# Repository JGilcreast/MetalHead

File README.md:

An opensource firmware and software drop-in replacement for the 85V Automatic Stirrup Bender by CRS Specialties Inc.
...short story behind the name...

# System Block Diagram

---

# Firmware
### HMI - Zephyr RTOS
* It's preferred to use CLion, 
* [Download](https://apps.microsoft.com/search?query=python&hl=en-US&gl=US) and install the latest version of python
* Install wget and 7Zip so that they're accessible via cmd:
  * `choco install wget 7zip`
* Verify python is accessible via cmd:
  * `python -V`
* Create python virtual environment
  * `cd MetalHead\firmware\interface-board-zephyr`
  * `python -m venv .\.venv`
* Enter python virtual environment
  * `.\.venv\Scripts\activate.bat`
* Update pip (optional)
  * `python.exe -m pip install --upgrade pip`
* Install west
  * `pip install west`
* Initiate the Zephyr-RTOS project
  * `west init`
* Set BOARD to rpi-pico
  * `west config zephyr.board rpi_pico`
* Pull the latest commits from Zephyr's github
  * `west update`
* Export a Zephyr CMake package. This allows CMake to automatically load boilerplate code required for building Zephyr applications.
  * `west zephyr-export`
  * > See: Computer\HKEY_CURRENT_USER\Software\Kitware\CMake\Packages
* Install additional packages need by west
  * `west packages pip --install`
* Install the Zephyr SDK
  * `west sdk install`
* Create a folder for bossac: C:\Program Files (x86)\BOSSA
* Copy bossac.exe to C:\Program Files (x86)\BOSSA
* Add C:\Program Files (x86)\BOSSA to PATH environment (use `sysdm.cpl`)
  * Make sure you can access bossac.exe. Open a new terminal and run: `bossac --help`
* Copy bossac.py from `MetalHead\firmware\interface-board-zephyr` to `MetalHead\firmware\interface-board-zephyr\zephyr\scripts\west_commands\runners`
* Start CLion
* Open our project: MetalHead\firmware\interface-board-zephyr\application
* Configure python interpreter for west
  * Go to File -> Settings -> Languages & Frameworks -> Python
  * Select the python interpreter from the list

To build a pristine copy of the firmware binary:[.gitignore](.gitignore)

  * `cd MetalHead\firmware\interface-board-zephyr`
  * `rmdir /q /s application\build`
  * Go back to CLion and reload West
  * Build, flash, etc

---

# Software
### HMI - Crude Edition

This is a simple unpolished version of the HMI app that will eventually run on the orange pi.
This version is mostly for implementation and testing purposes.
### HMI
The polished version of the HMI app. This app version be able to accomplish the following:
* Must be able to communicate with the interface board bi-directionally
* Display all relevant information in realtime.
* Recognize user input from the custom keypad
* Offer simple 'wizards' that visually guide operators to make common shapes

Nice to have features:
* Auto-update HMI software by communicating to a remote server
* Auto-update interface firmware by communicating to a remote server
* Include a section for custom stirrup calculators/guides
* Include instructional videos on using the machinery

---

# Hardware
### Interface Board

### Keypad

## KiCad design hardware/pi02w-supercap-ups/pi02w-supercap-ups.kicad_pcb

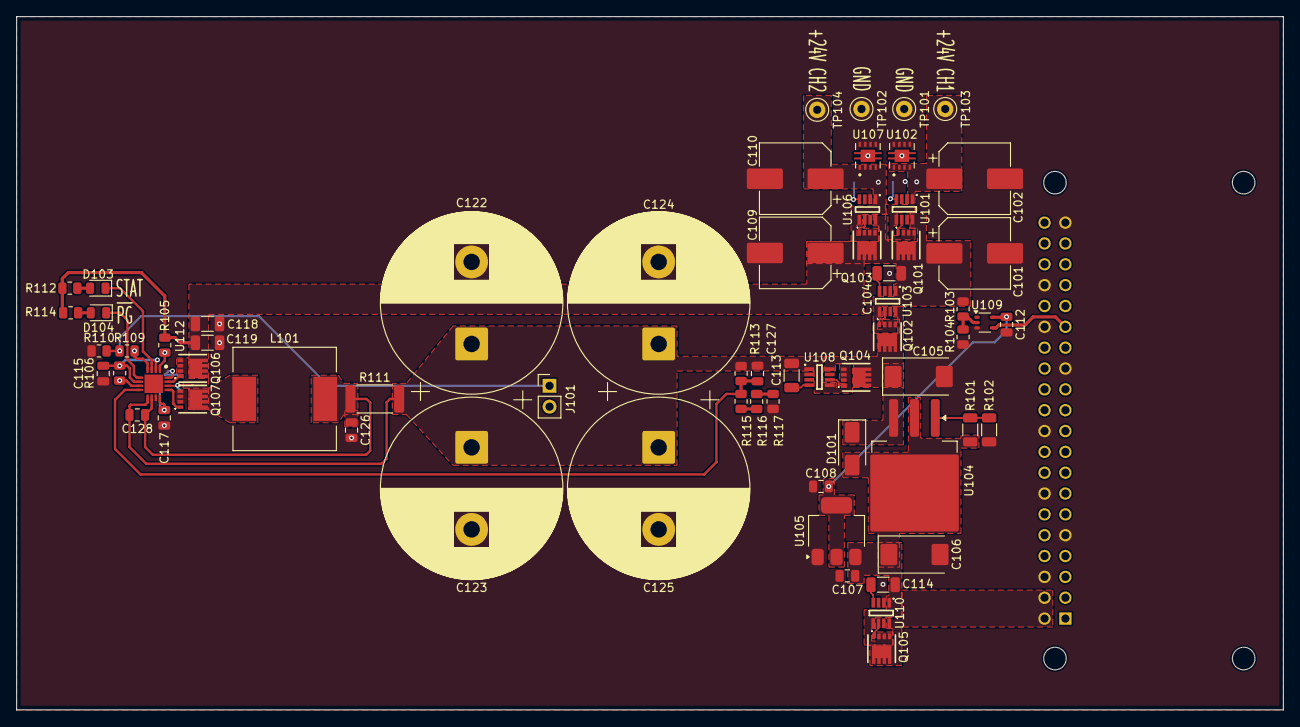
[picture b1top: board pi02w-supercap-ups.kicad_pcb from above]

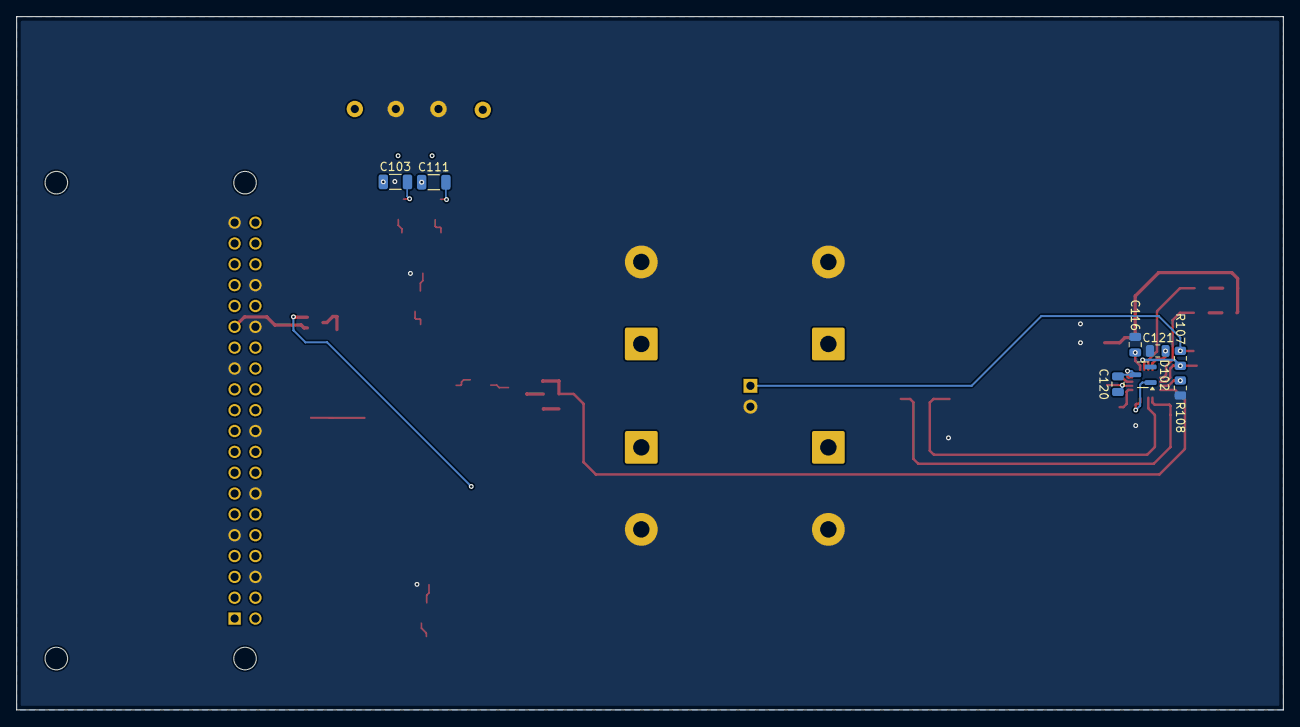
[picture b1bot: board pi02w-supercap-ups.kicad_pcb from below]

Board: 2 copper layers, 154.4 x 84.5 mm, 74 parts (8 on the bottom side), 40 nets.

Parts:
C101, C102, C109, C110: 330uF 25V; CP_Elec_8x10.5
C103, C104, C111, C113, C114: 100nF; C_1206_3216Metric
C105, C106: 10uF 50V; CP_EIA-7343-31_Kemet-D
C107, C108: 100nF; C_0805_2012Metric
C112, C115, C116, C117: 1uF; C_0805_2012Metric
C118, C119: 10uF; C_1206_3216Metric
C120, C121, C126, C128: 0.1uF; C_0805_2012Metric
C122, C123, C124, C125: 22000uF/25V; CP_Radial_D22.0mm_P10.00mm_SnapIn
C127: 22pF; C_0805_2012Metric
D101: 1N4002 M2; D_SMA
D102: BAT54C; SOT-23
D103: RED; LED_0805_2012Metric
D104: GREEN; LED_0805_2012Metric
J101: SEMITEC 103AT-2; PinHeader_1x02_P2.54mm_Vertical
L101: 10uH; L_12x12mm_H8mm
Q101, Q102, Q103, Q104, Q105, Q106, Q107: DMT6007LFG; DMP4013LFG7
R101: 300R; R_1206_3216Metric
R102: 900R; R_1206_3216Metric
R103: 62K; R_0805_2012Metric
R104: 10K; R_0805_2012Metric
R105: 10R; R_0805_2012Metric
R106: 100K; R_0805_2012Metric
R107: 9.31K; R_0805_2012Metric
R108: 22.1K; R_0805_2012Metric
R109: 100R; R_0805_2012Metric
R110: 430K; R_0805_2012Metric
R111: 10mR; R_2512_6332Metric
R112, R114: 2K2; R_0805_2012Metric
R113: 5K1; R_0805_2012Metric
R115: 430R; R_0805_2012Metric
R116: 56R; R_0805_2012Metric
R117: 3R; R_0805_2012Metric
TP101, TP102: 125-00869; TestPoint_Keystone_5000-5004_Miniature
TP103, TP104: 125-00868; TestPoint_Keystone_5000-5004_Miniature
U101, U103, U106, U108, U110: LM74700QDDFRQ1; SOT65P280X110-8N
U102, U107: TVS2701DRBR; IC_TVS2701DRBR
U104: LM1084-ADJ; TO-263-3_TabPin2
U105: AMS1117-3.3; SOT-223-3_TabPin2
U109: 74LVC1G14GW-Q100,1; SOT-353_SC-70-5
U111: RASPBERRY_PI_ZERO_2_W; MODULE_RASPBERRY_PI_ZERO_2_W
U112: BQ24640RVAR; QFN50P350X350X100-17N-D

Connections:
24VCC: C105.1, D101.1 (K), Q102.2 (D), Q104.2 (D), U103.8 (CATHODE), U104.3 (VI), U108.8 (CATHODE)
+3V3: C108.1, C112.1, U105.2 (VO), U109.5 (VCC)
+5V: C106.1, C107.1, C114.1, D101.2 (A), Q105.3 (S), R101.1, U104.2 (VO), U105.3 (VI), U110.1 (EN), U110.5 (ANODE)
+24V: C101.1, C104.1, C109.1, C118.1, C119.1, Q101.2 (D), Q102.3 (S), Q103.2 (D), Q106.2 (D), R103.1, R105.1, R112.1, R114.1, U101.8 (CATHODE), U103.1 (EN), U103.5 (ANODE), U106.8 (CATHODE)
/24VGATE: R103.2, R104.1, U109.2
/BTST: C120.1, D102.3 (K), U112.16 (BTST)
/HIDRV: Q106.1 (G), U112.15 (HIDRV)
/ISET: R106.2, R108.1, U112.7 (ISET)
/LODRV: Q107.1 (G), U112.13 (LODRV)
/PH: C120.2, L101.1, Q106.3 (S), Q107.2 (D), U112.14 (PH)
/PI02W5VCC: Q105.2 (D), U110.8 (CATHODE), U111.2 (5V_2), U111.4 (5V_4)
/PWRSNS: U109.4, U111.29 (GPIO5)
/REGN: C117.1, D102.1 (A), U112.12 (REGN)
/SRP: C126.2, C128.1, L101.2, R111.1, U112.10 (SRP)
/STAT: D103.1 (K), U112.3 (STAT)
/THERM: J101.1, R107.2, R109.1, R110.1
/TS: C121.1, R109.2, U112.4 (TS)
/VCC: C116.1, R105.2, U112.1 (VCC)
/VFB: C127.2, R113.2, R115.1, U112.8 (VFB)
/VREF: C115.1, R106.1, R107.1, U112.2 (CE), U112.6 (VREF)
/~PG: D104.1 (K), U112.5 (~PG)
GND: C101.2, C102.2, C105.2, C106.2, C107.2, C108.2, C109.2, C110.2, C112.2, C115.2, C116.2, C117.2, C118.2, C119.2, C121.2, C122.2, C123.2, C124.2, C125.2, C126.1, J101.2, Q107.3 (S), R102.2, R104.2, R108.2, R110.2, R117.2, TP101.1, TP102.1, U101.2 (GND), U102.5 (GND), U102.6 (GND), U102.7 (GND), U102.8 (GND), U103.2 (GND), U105.1 (GND), U106.2 (GND), U107.5 (GND), U107.6 (GND), U107.7 (GND), U107.8 (GND), U108.2 (GND), U109.3 (GND), U110.2 (GND), U111.6 (GND_6), U111.9 (GND_9), U111.14 (GND_14), U111.20 (GND_20), U111.25 (GND_25), U111.30 (GND_30), U111.34 (GND_34), U111.39 (GND_39), U112.11 (GND), U112.17 (EP)
unnamed: D103.2 (A), R112.2
unnamed: D104.2 (A), R114.2
unnamed: Q101.1 (G), U101.6 (GATE)
unnamed: Q102.1 (G), U103.6 (GATE)
unnamed: Q103.1 (G), U106.6 (GATE)
unnamed: Q104.1 (G), U108.6 (GATE)
unnamed: Q105.1 (G), U110.6 (GATE)
unnamed: R115.2, R116.1
unnamed: R116.2, R117.1
unnamed: C103.2, U101.4 (VCAP)
unnamed: C104.2, U103.4 (VCAP)
unnamed: R101.2, R102.1, U104.1 (ADJ)
unnamed: C111.2, U106.4 (VCAP)
unnamed: C113.2, U108.4 (VCAP)
unnamed: C114.2, U110.4 (VCAP)
RAW24V1: C102.1, C103.1, Q101.3 (S), TP103.1, U101.1 (EN), U101.5 (ANODE), U102.1 (IN), U102.2 (IN), U102.3 (IN), U102.4 (IN)
RAW24V2: C110.1, C111.1, Q103.3 (S), TP104.1, U106.1 (EN), U106.5 (ANODE), U107.1 (IN), U107.2 (IN), U107.3 (IN), U107.4 (IN)
UPS24V: C113.1, C122.1, C123.1, C124.1, C125.1, C127.1, C128.2, Q104.3 (S), R111.2, R113.1, U108.1 (EN), U108.5 (ANODE), U112.9 (SRN)

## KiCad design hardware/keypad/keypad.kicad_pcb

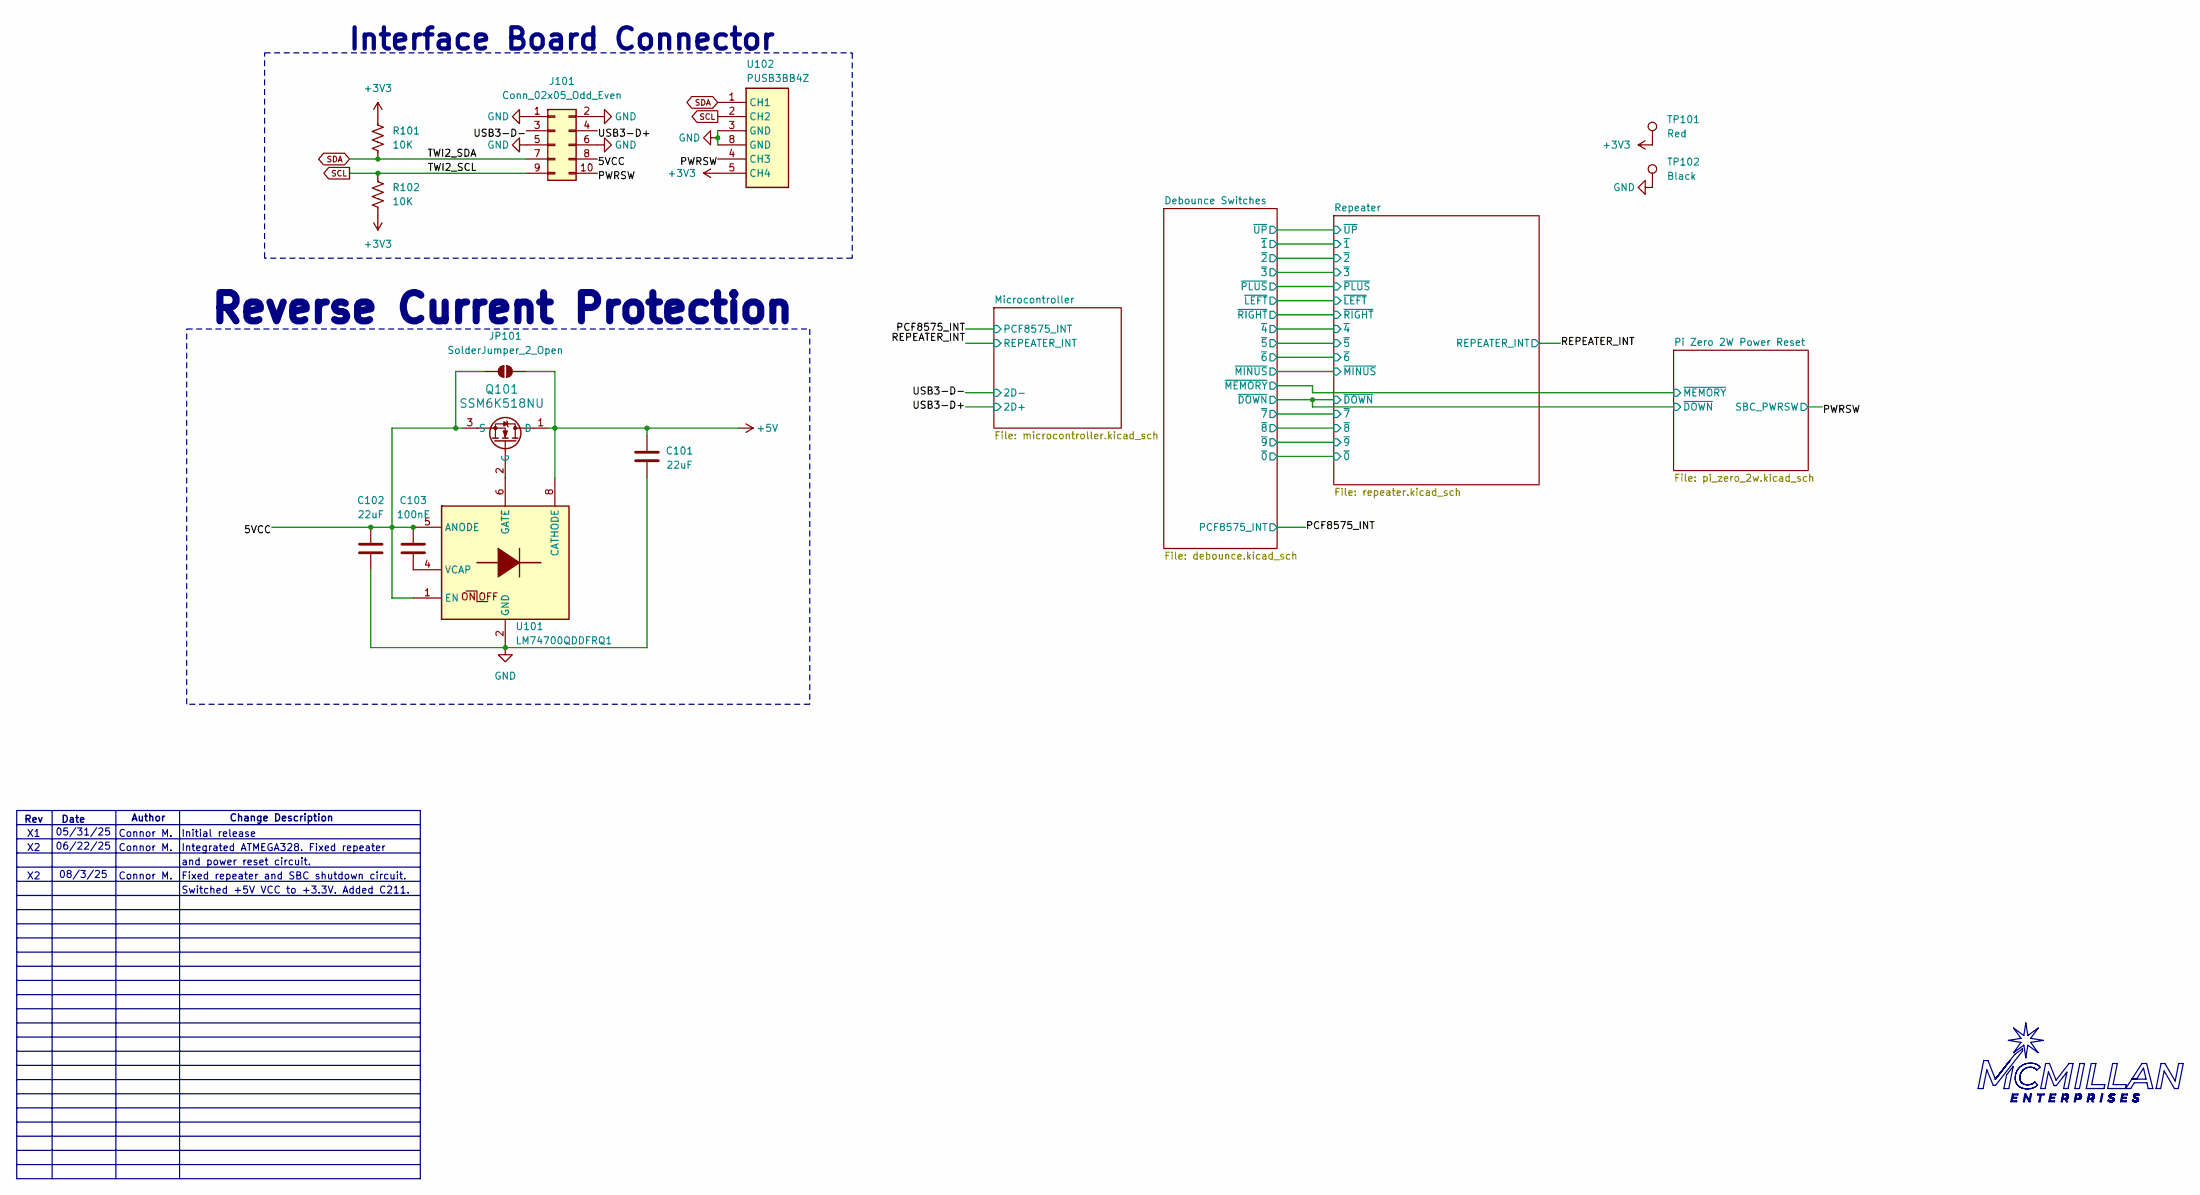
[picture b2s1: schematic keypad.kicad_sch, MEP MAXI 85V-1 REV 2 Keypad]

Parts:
C101, C102: 22uF; C_1206_3216Metric
C103: 100nF; C_1206_3216Metric
J101: Conn_02x05_Odd_Even; IDC-Header_2x05_P2.54mm_Vertical
JP101: SolderJumper_2_Open; SolderJumper-2_P1.3mm_Open_TrianglePad1.0x1.5mm
Q101: SSM6K518NU; SOT-1220UDFN6B_TOS
R101, R102: 10K; R_0805_2012Metric
TP101: Red; TestPoint_Keystone_5000-5004_Miniature
TP102: Black; TestPoint_Keystone_5000-5004_Miniature
U101: LM74700QDDFRQ1; SOT65P280X110-8N; Mouser Part Number 595-LM74700QDDFRQ1
U102: PUSB3BB4Z; SON50P100X250X50-10N; Mouser Part Number 771-PUSB3BB4Z

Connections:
+3V3: R101.1, R102.2, TP101.1, U102.5 (CH4); also elsewhere on the board
/5VCC: C102.1, C103.1, J101.8, JP101.1 (A), Q101.3 (S), U101.1 (EN), U101.5 (ANODE)
/PWRSW: J101.10, U102.4 (CH3); also elsewhere on the board
/USB3-D+: J101.4; also elsewhere on the board
/USB3-D-: J101.3; also elsewhere on the board
GND: C101.2, C102.2, J101.1, J101.2, J101.5, J101.6, TP102.1, U101.2 (GND), U102.3 (GND), U102.8 (GND); also elsewhere on the board
unnamed: C103.2, U101.4 (VCAP)
SCL: J101.9, R102.1, U102.2 (CH2); also elsewhere on the board
SDA: J101.7, R101.2, U102.1 (CH1); also elsewhere on the board

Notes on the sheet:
Change Description
Interface Board Connector
Integrated ATMEGA328. Fixed repeater
Date
Connor M.
and power reset circuit.
Initial release
Switched +5V VCC to +3.3V. Added C211.
08/3/25
Author
06/22/25
Reverse Current Protection
Fixed repeater and SBC shutdown circuit.
Rev
05/31/25

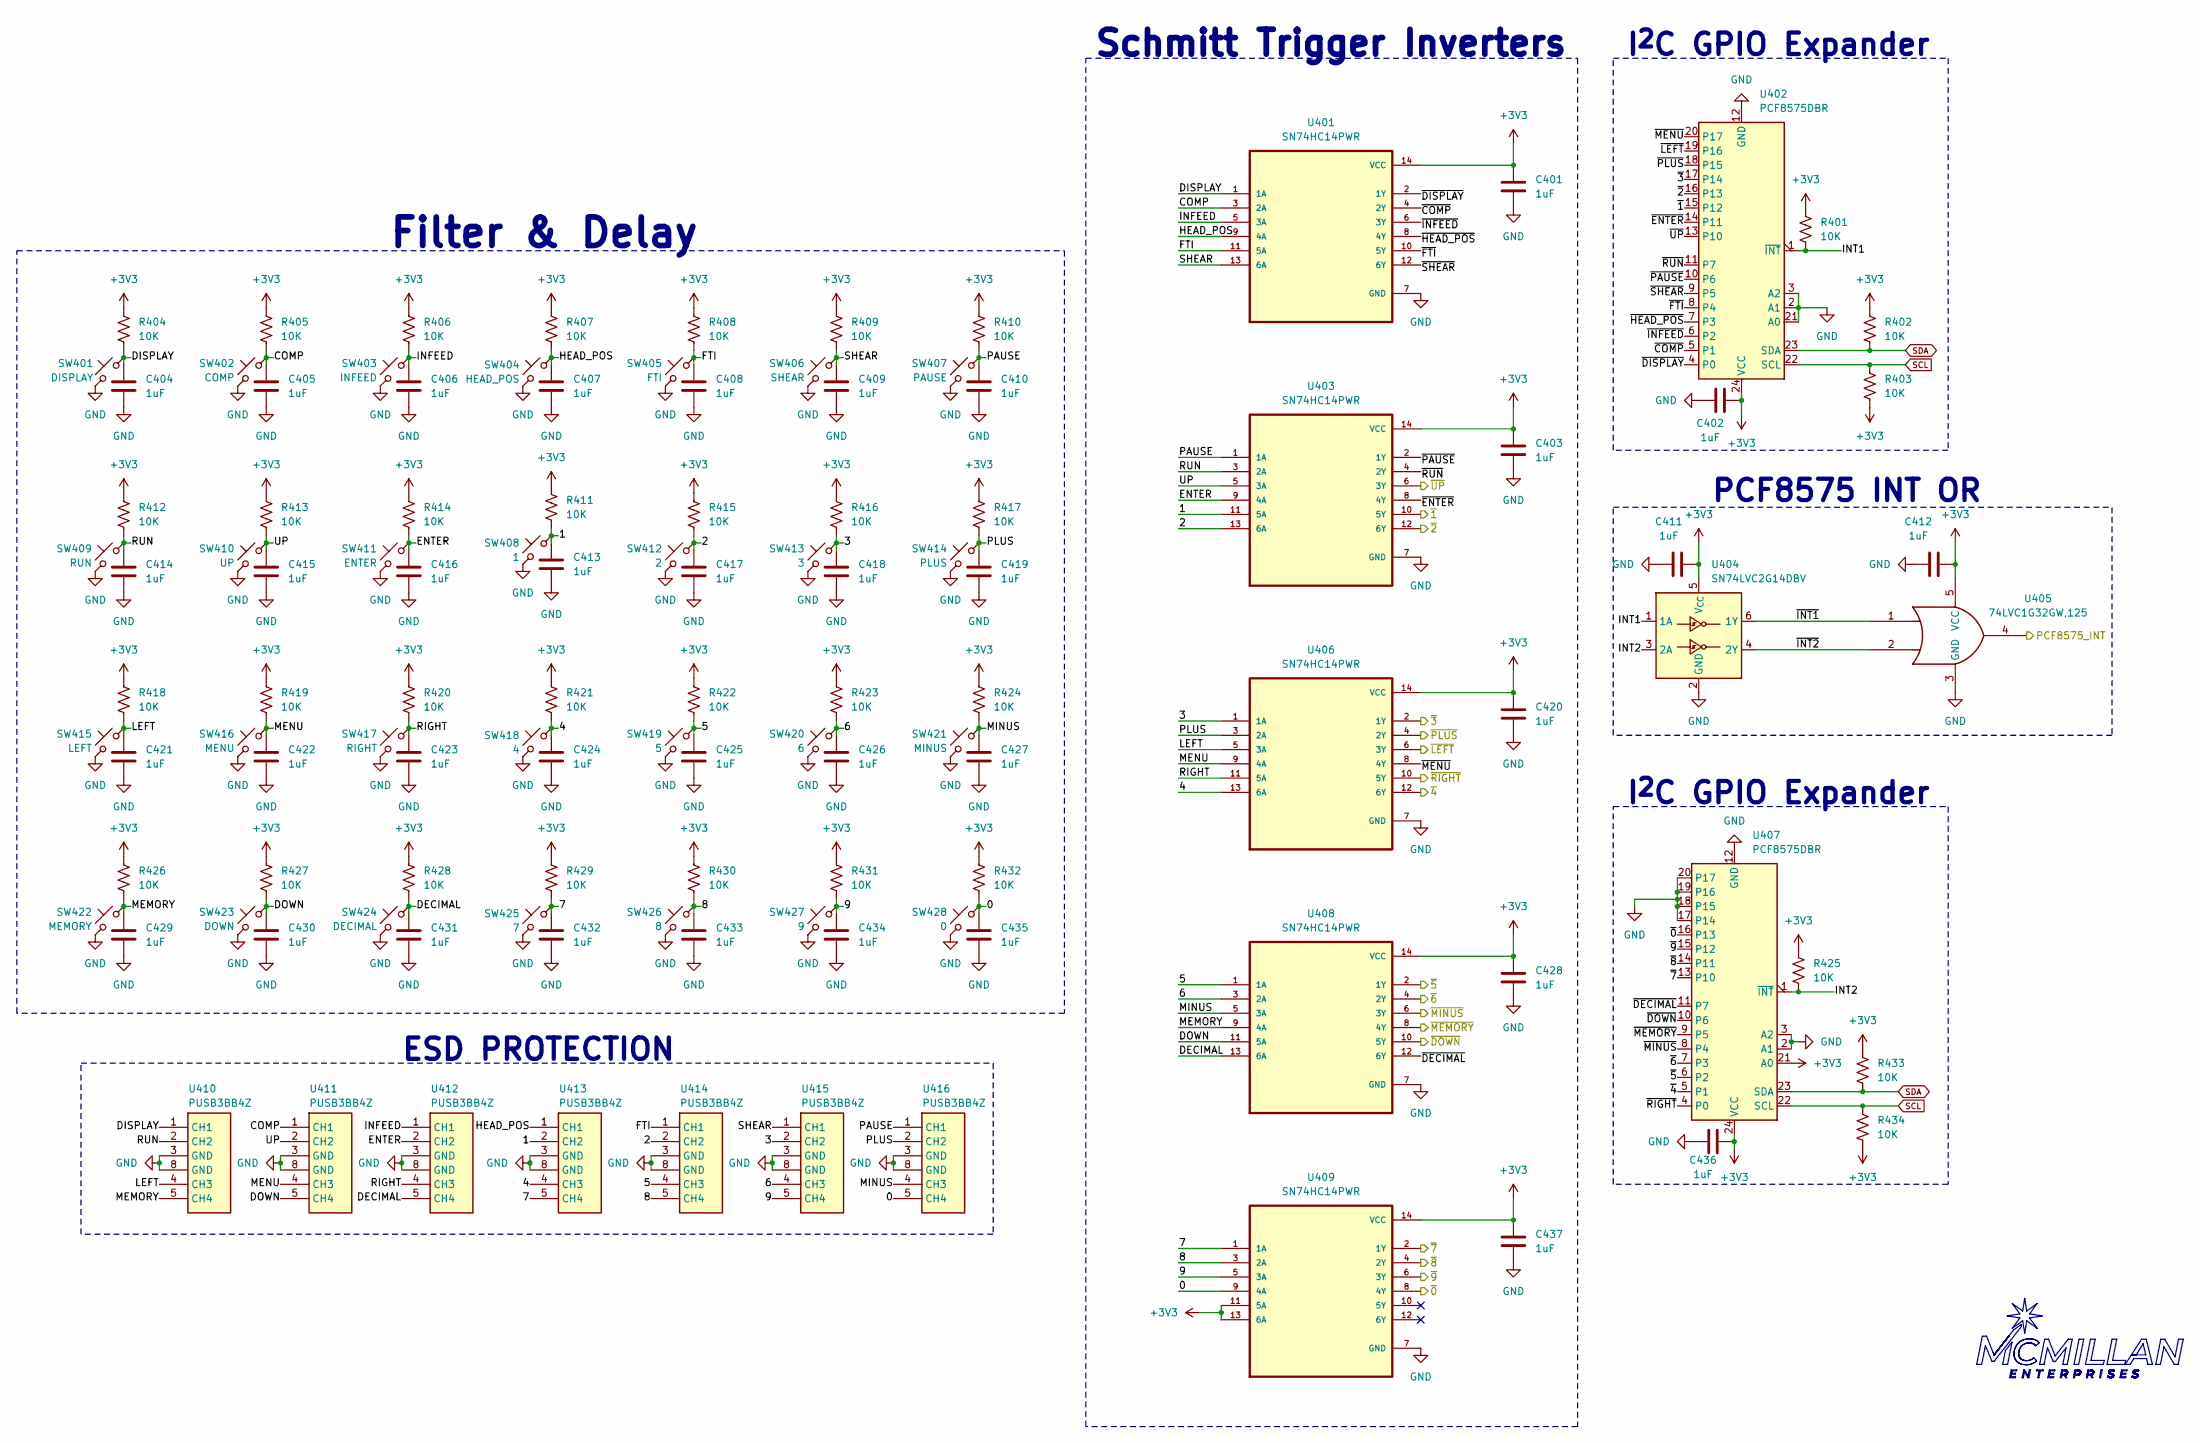
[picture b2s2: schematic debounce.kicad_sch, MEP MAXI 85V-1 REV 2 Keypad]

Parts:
C401, C402, C403, C404, C405, C406, C407, C408, C409, C410, C411, C412, C413, C414, C415, C416, C417, C418, C419, C420, C421, C422, C423, C424, C425, C426, C427, C428, C429, C430, C431, C432, C433, C434, C435, C436, C437: 1uF; C_0805_2012Metric
R401, R402, R403, R404, R405, R406, R407, R408, R409, R410, R411, R412, R413, R414, R415, R416, R417, R418, R419, R420, R421, R422, R423, R424, R425, R426, R427, R428, R429, R430, R431, R432, R433, R434: 10K; R_0805_2012Metric
SW401: DISPLAY; SW_SPST_Omron_B3F-40xx
SW402: COMP; SW_SPST_Omron_B3F-40xx
SW403: INFEED; SW_SPST_Omron_B3F-40xx
SW404: HEAD_POS; SW_SPST_Omron_B3F-40xx
SW405: FTI; SW_SPST_Omron_B3F-40xx
SW406: SHEAR; SW_SPST_Omron_B3F-40xx
SW407: PAUSE; SW_SPST_Omron_B3F-40xx
SW408: 1; SW_SPST_Omron_B3F-40xx
SW409: RUN; SW_SPST_Omron_B3F-40xx
SW410: UP; SW_SPST_Omron_B3F-40xx
SW411: ENTER; SW_SPST_Omron_B3F-40xx
SW412: 2; SW_SPST_Omron_B3F-40xx
SW413: 3; SW_SPST_Omron_B3F-40xx
SW414: PLUS; SW_SPST_Omron_B3F-40xx
SW415: LEFT; SW_SPST_Omron_B3F-40xx
SW416: MENU; SW_SPST_Omron_B3F-40xx
SW417: RIGHT; SW_SPST_Omron_B3F-40xx
SW418: 4; SW_SPST_Omron_B3F-40xx
SW419: 5; SW_SPST_Omron_B3F-40xx
SW420: 6; SW_SPST_Omron_B3F-40xx
SW421: MINUS; SW_SPST_Omron_B3F-40xx
SW422: MEMORY; SW_SPST_Omron_B3F-40xx
SW423: DOWN; SW_SPST_Omron_B3F-40xx
SW424: DECIMAL; SW_SPST_Omron_B3F-40xx
SW425: 7; SW_SPST_Omron_B3F-40xx
SW426: 8; SW_SPST_Omron_B3F-40xx
SW427: 9; SW_SPST_Omron_B3F-40xx
SW428: 0; SW_SPST_Omron_B3F-40xx
U401, U403, U406, U408, U409: SN74HC14PWR; SOP65P640X120-14N
U402, U407: PCF8575DBR; SSOP-24_5.3x8.2mm_P0.65mm
U404: SN74LVC2G14DBV; SOT95P280X145-6N
U405: 74LVC1G32GW,125; SOT-353_SC-70-5
U410, U411, U412, U413, U414, U415, U416: PUSB3BB4Z; SON50P100X250X50-10N; Mouser Part Number 771-PUSB3BB4Z

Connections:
+3V3: C401.1, C402.2, C403.1, C411.2, C412.2, C420.1, C428.1, C436.2, C437.1, R401.1, R402.1, R403.2, R404.1, R405.1, R406.1, R407.1, R408.1, R409.1, R410.1, R411.1, R412.1, R413.1, R414.1, R415.1, R416.1, R417.1, R418.1, R419.1, R420.1, R421.1, R422.1, R423.1, R424.1, R425.1, R426.1, R427.1, R428.1, R429.1, R430.1, R431.1, R432.1, R433.1, R434.2, U401.14 (VCC), U402.24 (VCC), U403.14 (VCC), U404.5 (V_{CC}), U405.5 (VCC), U406.14 (VCC), U407.21 (A0), U407.24 (VCC), U408.14 (VCC), U409.11 (5A), U409.13 (6A), U409.14 (VCC); also elsewhere on the board
/Debounce Switches/0: C435.1, R432.2, SW428.2, U409.9 (4A), U416.5 (CH4)
/Debounce Switches/1: C413.1, R411.2, SW408.2, U403.11 (5A), U413.2 (CH2)
/Debounce Switches/2: C417.1, R415.2, SW412.2, U403.13 (6A), U414.2 (CH2)
/Debounce Switches/3: C418.1, R416.2, SW413.2, U406.1 (1A), U415.2 (CH2)
/Debounce Switches/4: C424.1, R421.2, SW418.2, U406.13 (6A), U413.4 (CH3)
/Debounce Switches/5: C425.1, R422.2, SW419.2, U408.1 (1A), U414.4 (CH3)
/Debounce Switches/6: C426.1, R423.2, SW420.2, U408.3 (2A), U415.4 (CH3)
/Debounce Switches/7: C432.1, R429.2, SW425.2, U409.1 (1A), U413.5 (CH4)
/Debounce Switches/8: C433.1, R430.2, SW426.2, U409.3 (2A), U414.5 (CH4)
/Debounce Switches/9: C434.1, R431.2, SW427.2, U409.5 (3A), U415.5 (CH4)
/Debounce Switches/COMP: C405.1, R405.2, SW402.2, U401.3 (2A), U411.1 (CH1)
/Debounce Switches/DECIMAL: C431.1, R428.2, SW424.2, U408.13 (6A), U412.5 (CH4)
/Debounce Switches/DISPLAY: C404.1, R404.2, SW401.2, U401.1 (1A), U410.1 (CH1)
/Debounce Switches/DOWN: C430.1, R427.2, SW423.2, U408.11 (5A), U411.5 (CH4)
/Debounce Switches/ENTER: C416.1, R414.2, SW411.2, U403.9 (4A), U412.2 (CH2)
/Debounce Switches/FTI: C408.1, R408.2, SW405.2, U401.11 (5A), U414.1 (CH1)
/Debounce Switches/HEAD_POS: C407.1, R407.2, SW404.2, U401.9 (4A), U413.1 (CH1)
/Debounce Switches/INFEED: C406.1, R406.2, SW403.2, U401.5 (3A), U412.1 (CH1)
/Debounce Switches/INT1: R401.2, U402.1 (~INT), U404.1 (1A)
/Debounce Switches/INT2: R425.2, U404.3 (2A), U407.1 (~INT)
/Debounce Switches/LEFT: C421.1, R418.2, SW415.2, U406.5 (3A), U410.4 (CH3)
/Debounce Switches/MEMORY: C429.1, R426.2, SW422.2, U408.9 (4A), U410.5 (CH4)
/Debounce Switches/MENU: C422.1, R419.2, SW416.2, U406.9 (4A), U411.4 (CH3)
/Debounce Switches/MINUS: C427.1, R424.2, SW421.2, U408.5 (3A), U416.4 (CH3)
/Debounce Switches/PAUSE: C410.1, R410.2, SW407.2, U403.1 (1A), U416.1 (CH1)
/Debounce Switches/PLUS: C419.1, R417.2, SW414.2, U406.3 (2A), U416.2 (CH2)
/Debounce Switches/RIGHT: C423.1, R420.2, SW417.2, U406.11 (5A), U412.4 (CH3)
/Debounce Switches/RUN: C414.1, R412.2, SW409.2, U403.3 (2A), U410.2 (CH2)
/Debounce Switches/SHEAR: C409.1, R409.2, SW406.2, U401.13 (6A), U415.1 (CH1)
/Debounce Switches/UP: C415.1, R413.2, SW410.2, U403.5 (3A), U411.2 (CH2)
/Debounce Switches/~0: U407.16 (P13), U409.8 (4Y); also elsewhere on the board
/Debounce Switches/~1: U402.15 (P12), U403.10 (5Y); also elsewhere on the board
/Debounce Switches/~2: U402.16 (P13), U403.12 (6Y); also elsewhere on the board
/Debounce Switches/~3: U402.17 (P14), U406.2 (1Y); also elsewhere on the board
/Debounce Switches/~4: U406.12 (6Y), U407.5 (P1); also elsewhere on the board
/Debounce Switches/~5: U407.6 (P2), U408.2 (1Y); also elsewhere on the board
/Debounce Switches/~6: U407.7 (P3), U408.4 (2Y); also elsewhere on the board
/Debounce Switches/~7: U407.13 (P10), U409.2 (1Y); also elsewhere on the board
/Debounce Switches/~8: U407.14 (P11), U409.4 (2Y); also elsewhere on the board
/Debounce Switches/~9: U407.15 (P12), U409.6 (3Y); also elsewhere on the board
/Debounce Switches/~COMP: U401.4 (2Y), U402.5 (P1)
/Debounce Switches/~DECIMAL: U407.11 (P7), U408.12 (6Y)
/Debounce Switches/~DISPLAY: U401.2 (1Y), U402.4 (P0)
/Debounce Switches/~DOWN: U407.10 (P6), U408.10 (5Y); also elsewhere on the board
/Debounce Switches/~ENTER: U402.14 (P11), U403.8 (4Y)
/Debounce Switches/~FTI: U401.10 (5Y), U402.8 (P4)
/Debounce Switches/~HEAD_POS: U401.8 (4Y), U402.7 (P3)
/Debounce Switches/~INFEED: U401.6 (3Y), U402.6 (P2)
/Debounce Switches/~INT1: U404.6 (1Y), U405.1
/Debounce Switches/~INT2: U404.4 (2Y), U405.2
/Debounce Switches/~LEFT: U402.19 (P16), U406.6 (3Y); also elsewhere on the board
/Debounce Switches/~MEMORY: U407.9 (P5), U408.8 (4Y); also elsewhere on the board
/Debounce Switches/~MENU: U402.20 (P17), U406.8 (4Y)
/Debounce Switches/~MINUS: U407.8 (P4), U408.6 (3Y); also elsewhere on the board
/Debounce Switches/~PAUSE: U402.10 (P6), U403.2 (1Y)
/Debounce Switches/~PLUS: U402.18 (P15), U406.4 (2Y); also elsewhere on the board
/Debounce Switches/~RIGHT: U406.10 (5Y), U407.4 (P0); also elsewhere on the board
/Debounce Switches/~RUN: U402.11 (P7), U403.4 (2Y)
/Debounce Switches/~SHEAR: U401.12 (6Y), U402.9 (P5)
/Debounce Switches/~UP: U402.13 (P10), U403.6 (3Y); also elsewhere on the board
/PCF8575_INT: U405.4; also elsewhere on the board
GND: C401.2, C402.1, C403.2, C404.2, C405.2, C406.2, C407.2, C408.2, C409.2, C410.2, C411.1, C412.1, C413.2, C414.2, C415.2, C416.2, C417.2, C418.2, C419.2, C420.2, C421.2, C422.2, C423.2, C424.2, C425.2, C426.2, C427.2, C428.2, C429.2, C430.2, C431.2, C432.2, C433.2, C434.2, C435.2, C436.1, C437.2, SW401.1, SW402.1, SW403.1, SW404.1, SW405.1, SW406.1, SW407.1, SW408.1, SW409.1, SW410.1, SW411.1, SW412.1, SW413.1, SW414.1, SW415.1, SW416.1, SW417.1, SW418.1, SW419.1, SW420.1, SW421.1, SW422.1, SW423.1, SW424.1, SW425.1, SW426.1, SW427.1, SW428.1, U401.7 (GND), U402.2 (A1), U402.3 (A2), U402.12 (GND), U402.21 (A0), U403.7 (GND), U404.2 (GND), U405.3 (GND), U406.7 (GND), U407.2 (A1), U407.3 (A2), U407.12 (GND), U407.17 (P14), U407.18 (P15), U407.19 (P16), U407.20 (P17), U408.7 (GND), U409.7 (GND), U410.3 (GND), U410.8 (GND), U411.3 (GND), U411.8 (GND), U412.3 (GND), U412.8 (GND), U413.3 (GND), U413.8 (GND), U414.3 (GND), U414.8 (GND), U415.3 (GND), U415.8 (GND), U416.3 (GND), U416.8 (GND); also elsewhere on the board
SCL: R403.1, R434.1, U402.22 (SCL), U407.22 (SCL); also elsewhere on the board
SDA: R402.2, R433.2, U402.23 (SDA), U407.23 (SDA); also elsewhere on the board

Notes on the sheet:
I^{2}C GPIO Expander
Schmitt Trigger Inverters
PCF8575 INT OR
ESD PROTECTION
Filter & Delay

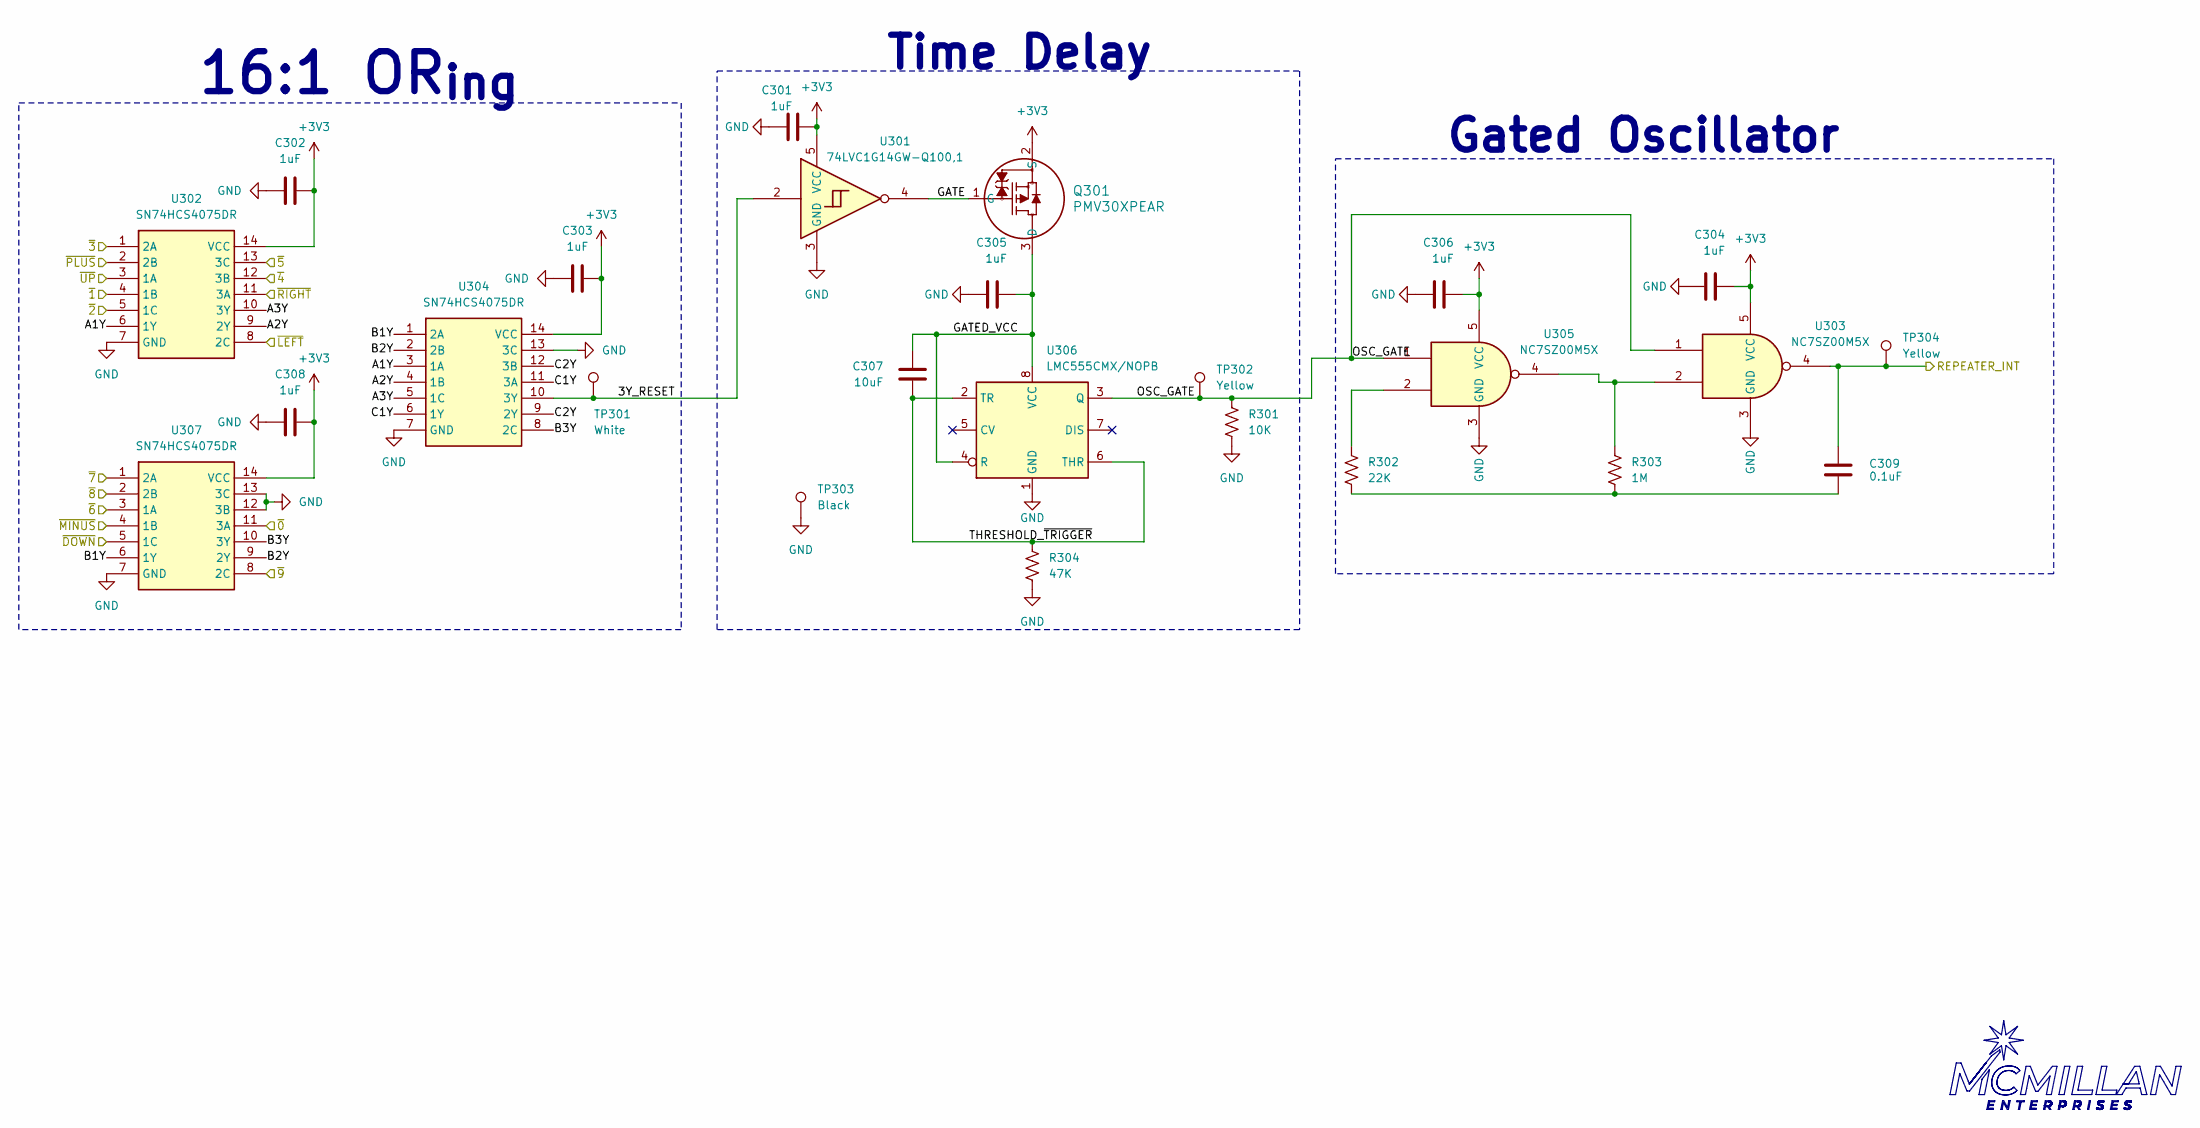
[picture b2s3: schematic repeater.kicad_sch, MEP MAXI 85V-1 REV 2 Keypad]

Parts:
C301, C302, C303, C304, C305, C306, C308: 1uF; C_0805_2012Metric
C307: 10uF; C_0805_2012Metric
C309: 0.1uF; C_0805_2012Metric
Q301: PMV30XPEAR; SOT-23-3
R301: 10K; R_0805_2012Metric
R302: 22K; R_0805_2012Metric
R303: 1M; R_0805_2012Metric
R304: 47K; R_0805_2012Metric
TP301: White; TestPoint_Keystone_5000-5004_Miniature
TP302, TP304: Yellow; TestPoint_Keystone_5000-5004_Miniature
TP303: Black; TestPoint_Keystone_5000-5004_Miniature
U301: 74LVC1G14GW-Q100,1; SOT-353_SC-70-5
U302, U304, U307: SN74HCS4075DR; SOIC127P600X175-14N; Mouser Part Number 595-SN74HCS4075DR
U303, U305: NC7SZ00M5X; SOT-23-5
U306: LMC555CMX/NOPB; SOIC-8_3.9x4.9mm_P1.27mm

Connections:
+3V3: C301.1, C302.2, C303.2, C304.1, C306.1, C308.2, Q301.2 (S), U301.5 (VCC), U302.14 (VCC), U303.5 (VCC), U304.14 (VCC), U305.5 (VCC), U307.14 (VCC); also elsewhere on the board
/Debounce Switches/~0: U307.11 (3A); also elsewhere on the board
/Debounce Switches/~1: U302.4 (1B); also elsewhere on the board
/Debounce Switches/~2: U302.5 (1C); also elsewhere on the board
/Debounce Switches/~3: U302.1 (2A); also elsewhere on the board
/Debounce Switches/~4: U302.12 (3B); also elsewhere on the board
/Debounce Switches/~5: U302.13 (3C); also elsewhere on the board
/Debounce Switches/~6: U307.3 (1A); also elsewhere on the board
/Debounce Switches/~7: U307.1 (2A); also elsewhere on the board
/Debounce Switches/~8: U307.2 (2B); also elsewhere on the board
/Debounce Switches/~9: U307.8 (2C); also elsewhere on the board
/Debounce Switches/~DOWN: U307.5 (1C); also elsewhere on the board
/Debounce Switches/~LEFT: U302.8 (2C); also elsewhere on the board
/Debounce Switches/~MINUS: U307.4 (1B); also elsewhere on the board
/Debounce Switches/~PLUS: U302.2 (2B); also elsewhere on the board
/Debounce Switches/~RIGHT: U302.11 (3A); also elsewhere on the board
/Debounce Switches/~UP: U302.3 (1A); also elsewhere on the board
/REPEATER_INT: C309.1, TP304.1, U303.4; also elsewhere on the board
/Repeater/3Y_RESET: TP301.1, U301.2, U304.10 (3Y)
/Repeater/A1Y: U302.6 (1Y), U304.3 (1A)
/Repeater/A2Y: U302.9 (2Y), U304.4 (1B)
/Repeater/A3Y: U302.10 (3Y), U304.5 (1C)
/Repeater/B1Y: U304.1 (2A), U307.6 (1Y)
/Repeater/B2Y: U304.2 (2B), U307.9 (2Y)
/Repeater/B3Y: U304.8 (2C), U307.10 (3Y)
/Repeater/C1Y: U304.6 (1Y), U304.11 (3A)
/Repeater/C2Y: U304.9 (2Y), U304.12 (3B)
/Repeater/GATE: Q301.1 (G), U301.4
/Repeater/GATED_VCC: C305.1, C307.1, Q301.3 (D), U306.4 (R), U306.8 (VCC)
/Repeater/OSC_GATE: R301.1, TP302.1, U303.1, U305.1, U306.3 (Q)
/Repeater/THRESHOLD_~TRIGGER: C307.2, R304.1, U306.2 (TR), U306.6 (THR)
GND: C301.2, C302.1, C303.1, C304.2, C305.2, C306.2, C308.1, R301.2, R304.2, TP303.1, U301.3 (GND), U302.7 (GND), U303.3 (GND), U304.7 (GND), U304.13 (3C), U305.3 (GND), U306.1 (GND), U307.7 (GND), U307.12 (3B), U307.13 (3C); also elsewhere on the board
unnamed: C309.2, R302.2, R303.2
unnamed: R302.1, U305.2
unnamed: R303.1, U303.2, U305.4

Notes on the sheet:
Gated Oscillator
Time Delay
16:1 OR_{ing}
